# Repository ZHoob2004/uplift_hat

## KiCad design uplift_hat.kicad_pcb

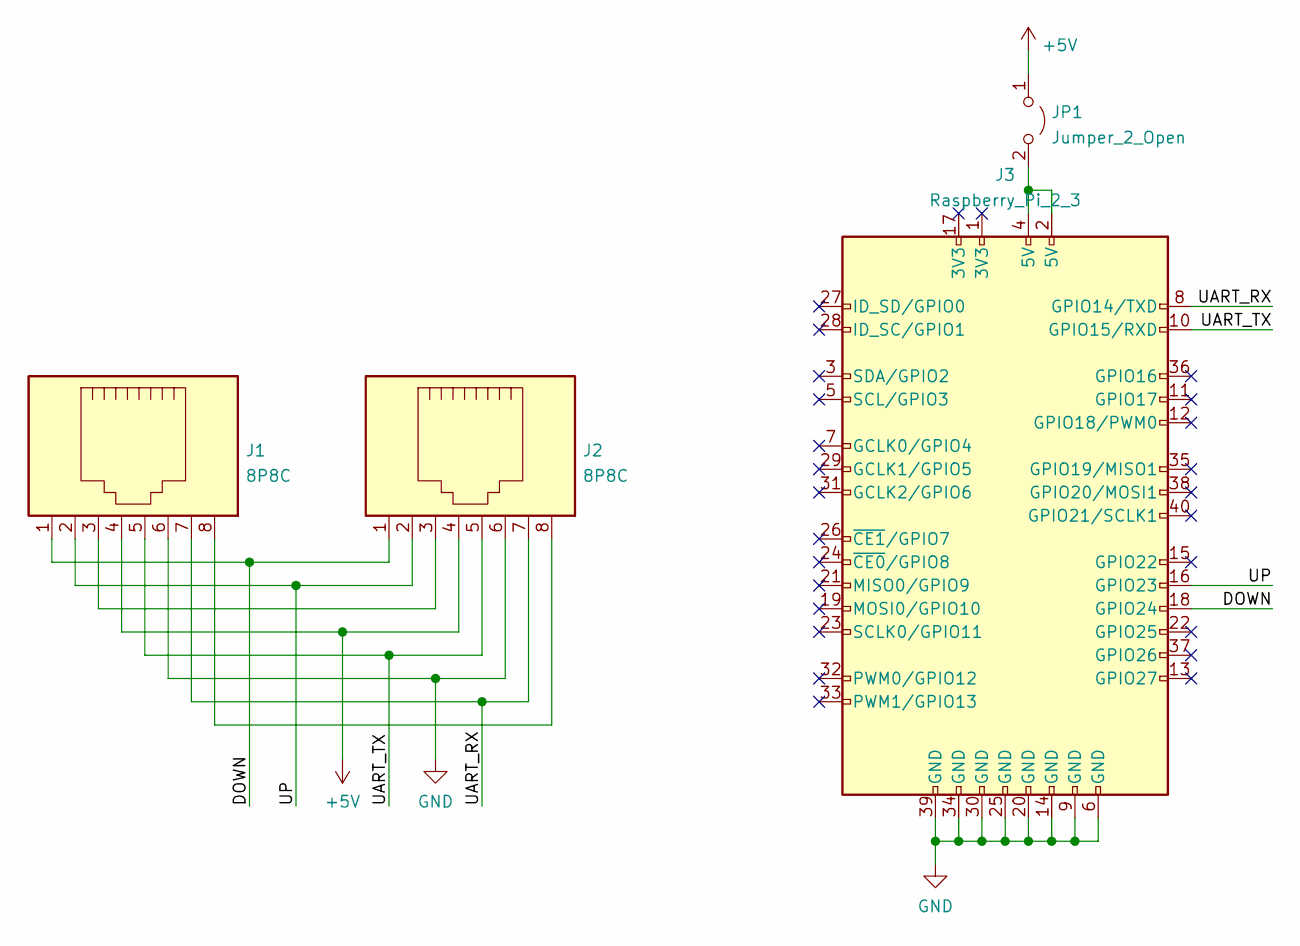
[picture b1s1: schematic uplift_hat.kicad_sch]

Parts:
J1, J2: 8P8C; RJ45_Amphenol_54602-x08_Horizontal
J3: Raspberry_Pi_2_3; PinSocket_2x20_P2.54mm_Vertical
JP1: Jumper_2_Open; SolderJumper-2_P1.3mm_Open_TrianglePad1.0x1.5mm

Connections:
+5V: J1.4, J2.4, JP1.1 (A)
/DOWN: J1.1, J2.1, J3.18 (GPIO24)
/UART_RX: J1.7, J2.7, J3.8 (GPIO14/TXD)
/UART_TX: J1.5, J2.5, J3.10 (GPIO15/RXD)
/UP: J1.2, J2.2, J3.16 (GPIO23)
GND: J1.6, J2.6, J3.6 (GND), J3.9 (GND), J3.14 (GND), J3.20 (GND), J3.25 (GND), J3.30 (GND), J3.34 (GND), J3.39 (GND)
unnamed: J1.3, J2.3
unnamed: J1.8, J2.8
unnamed: J3.2 (5V), J3.4 (5V), JP1.2 (B)

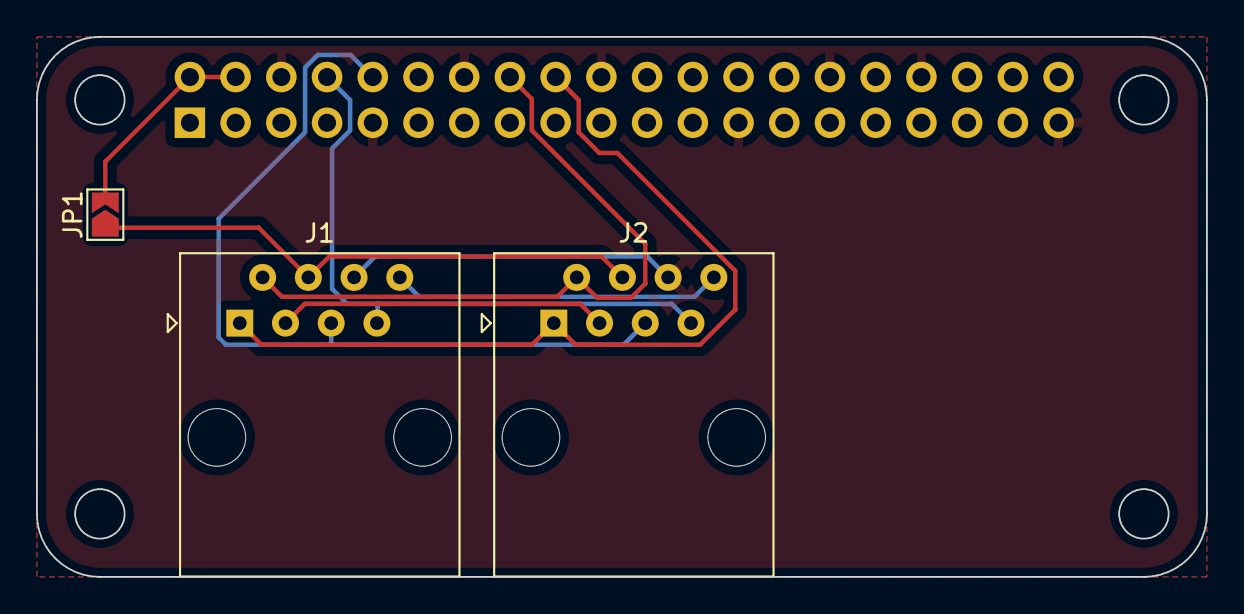
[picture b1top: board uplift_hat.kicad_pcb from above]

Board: 2 copper layers, 65.0 x 30.0 mm, 4 parts (1 on the bottom side), 9 nets.

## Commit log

2021-08-22 Fixed GPIO orientation
2021-08-23 Fixed design rules and generated gerbers
2021-08-23 Changed mounting holes to filled holes instead of outline only
